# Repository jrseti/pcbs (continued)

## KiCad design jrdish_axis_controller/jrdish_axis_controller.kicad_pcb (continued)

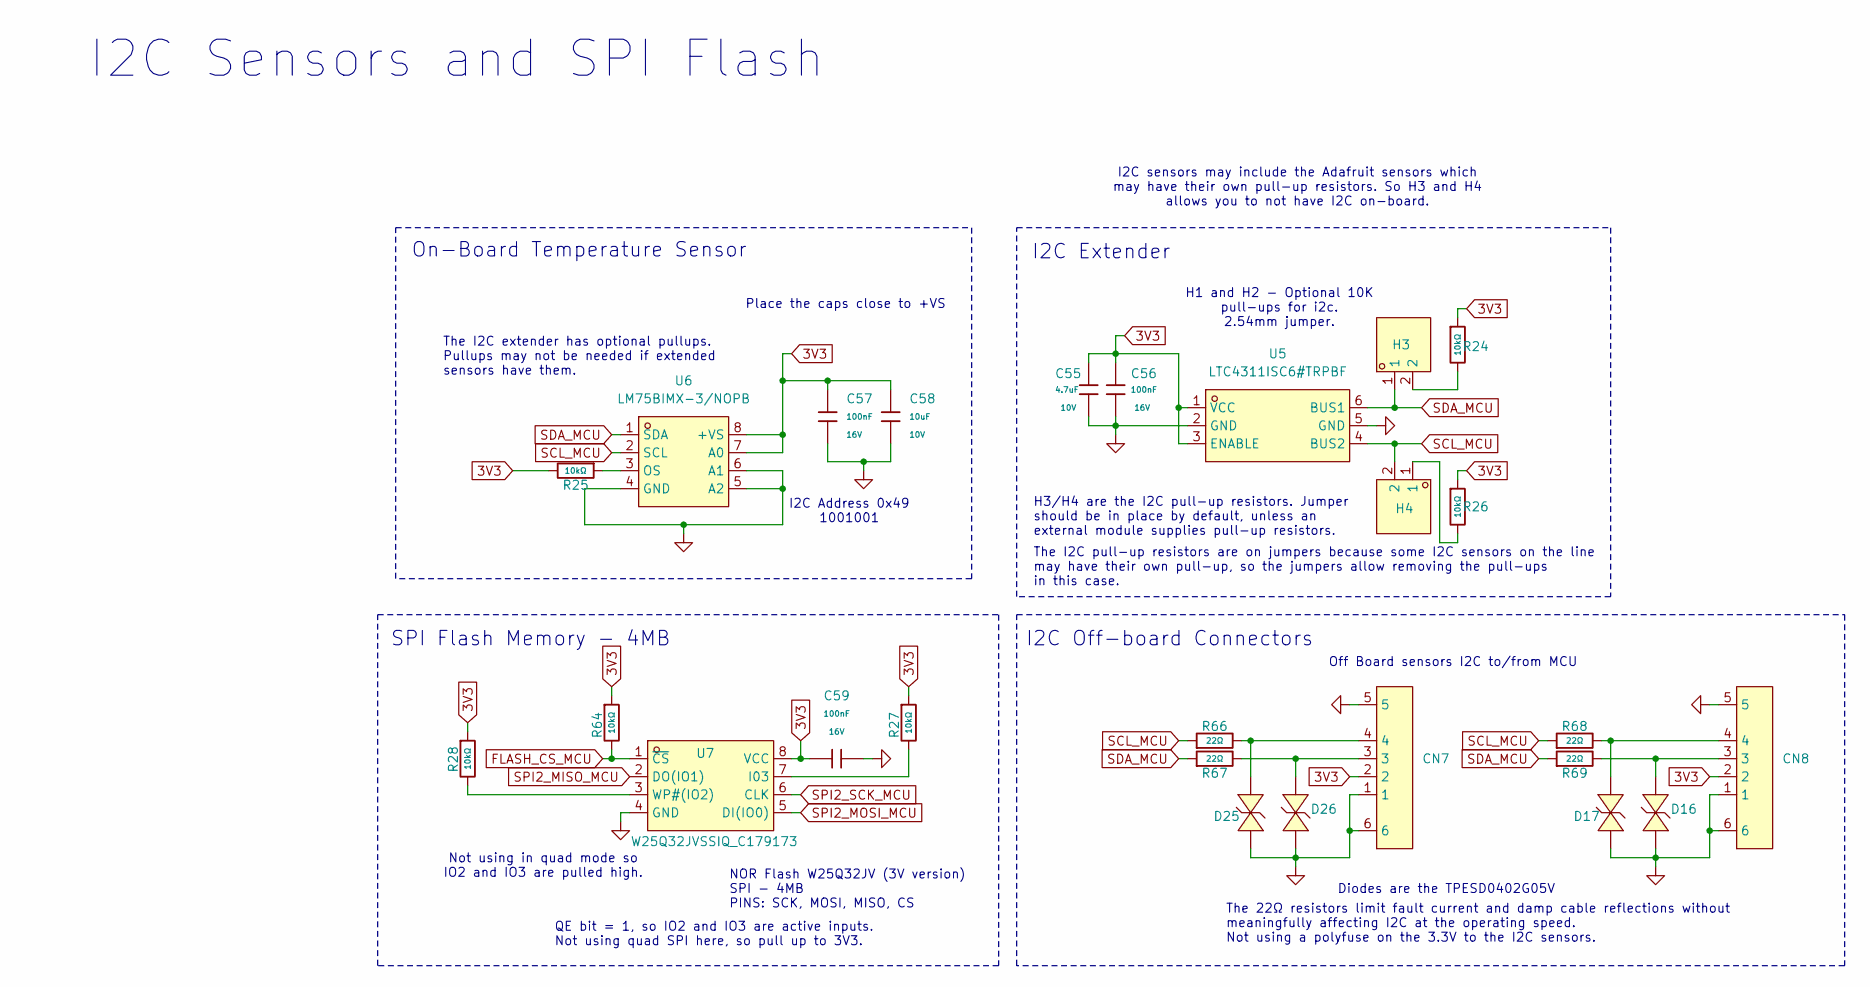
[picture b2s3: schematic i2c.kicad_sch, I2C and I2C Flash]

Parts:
C55: 4.7uF; C_0402; Voltage Rated 10V; Tolerance ±20%; Part CL05A475MP5NRNC; LCSC C23733
C56, C57, C59: 100nF; C_0402; Voltage Rated 16V; Tolerance ±10%; Part CL05B104KO5NNNC; LCSC C1525
C58: 10uF; C_0603; Voltage Rated 10V; Tolerance ±10%; Part CL10A106KP8NNNC; LCSC C19702
CN7, CN8: SM04B-SRSS-TB (LF)(SN); CONN-SMD_4P-P1.00_SM04B-SRSS-TB-LF-SN; LCSC Part C160404
D16, D17, D25, D26: TPESD0402G05V; D0402-BI; LCSC Part C558615
H3, H4: 210S-1*2P L=11.6MMGold-plated black; HDR-TH_2P-P2.54-V-M-1; MPN B-2100S02P-A110; LCSC Part C124375
R24, R25, R26, R27, R28, R64: 10kΩ; R_0402; Overload Voltage (Max) 50V; Tolerance ±1%; Part 0402WGF1002TCE; LCSC C173683
R66, R67, R68, R69: 22Ω; R_0402; Overload Voltage (Max) 50V; Tolerance ±1%; Part 0402WGF220JTCE; LCSC C25092
U5: LTC4311ISC6#TRPBF; SC-70-6_L2.2-W1.3-P0.65-LS2.2-BL; LCSC Part C688097
U6: LM75BIMX-3/NOPB; SOIC-8_L4.9-W3.9-P1.27-LS6.0-BL; MPN LM75BIMX-3/NOPB; LCSC Part C477980
U7: W25Q32JVSSIQ_C179173; SOIC-8_L5.3-W5.3-P1.27-LS8.0-BL; MPN W25Q32JVSSIQ; LCSC Part C179173

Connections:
FLASH_CS_MCU: R64.2, U7.1 (~CS); also elsewhere on the board
GND: C55.2, C56.2, C57.2, C58.2, C59.2, CN7.1, CN7.5, CN7.6, CN8.1, CN8.5, CN8.6, D16.2 (A), D17.2 (A), D25.2 (A), D26.2 (A), U5.2 (GND), U5.5 (GND), U6.4 (GND), U6.5 (A2), U6.6 (A1), U7.4 (GND); also elsewhere on the board
unnamed: CN8.3, D16.1 (K), R69.2
unnamed: CN8.4, D17.1 (K), R68.2
unnamed: CN7.4, D25.1 (K), R66.2
unnamed: CN7.3, D26.1 (K), R67.2
unnamed: H3.2, R24.2
unnamed: H4.1, R26.2
unnamed: R25.1, U6.3 (OS)
unnamed: R27.2, U7.7 (I03)
unnamed: R28.2, U7.3 (WP#(IO2))
SCL_MCU: H4.2, R66.1, R68.1, U5.4 (BUS2), U6.2 (SCL); also elsewhere on the board
SDA_MCU: H3.1, R67.1, R69.1, U5.6 (BUS1), U6.1 (SDA); also elsewhere on the board
SPI2_MISO_MCU: U7.2 (DO(IO1)); also elsewhere on the board
SPI2_MOSI_MCU: U7.5 (DI(IO0)); also elsewhere on the board
SPI2_SCK_MCU: U7.6 (CLK); also elsewhere on the board

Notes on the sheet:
H1 and H2 - Optional 10K pull-ups for i2c. 2.54mm jumper.
I2C Address 0x49 1001001
Off Board sensors I2C to/from MCU
NOR Flash W25Q32JV (3V version) SPI - 4MB PINS: SCK, MOSI, MISO, CS
I2C Off-board Connectors
I2C Extender
I2C Sensors and SPI Flash
H3/H4 are the I2C pull-up resistors. Jumper should be in place by default, unless an external module supplies pull-up resistors.
QE bit = 1, so IO2 and IO3 are active inputs. Not using quad SPI here, so pull up to 3V3.
I2C sensors may include the Adafruit sensors which may have their own pull-up resistors. So H3 and H4 allows you to not have I2C on-board.
The I2C pull-up resistors are on jumpers because some I2C sensors on the line may have their own pull-up, so the jumpers allow removing the pull-ups in this case.
Not using in quad mode so IO2 and IO3 are pulled high.
Place the caps close to +VS
On-Board Temperature Sensor
The I2C extender has optional pullups. Pullups may not be needed if extended sensors have them.
SPI Flash Memory - 4MB
The 22Ω resistors limit fault current and damp cable reflections without meaningfully affecting I2C at the operating speed. Not using a polyfuse on the 3.3V to the I2C sensors.
Diodes are the TPESD0402G05V

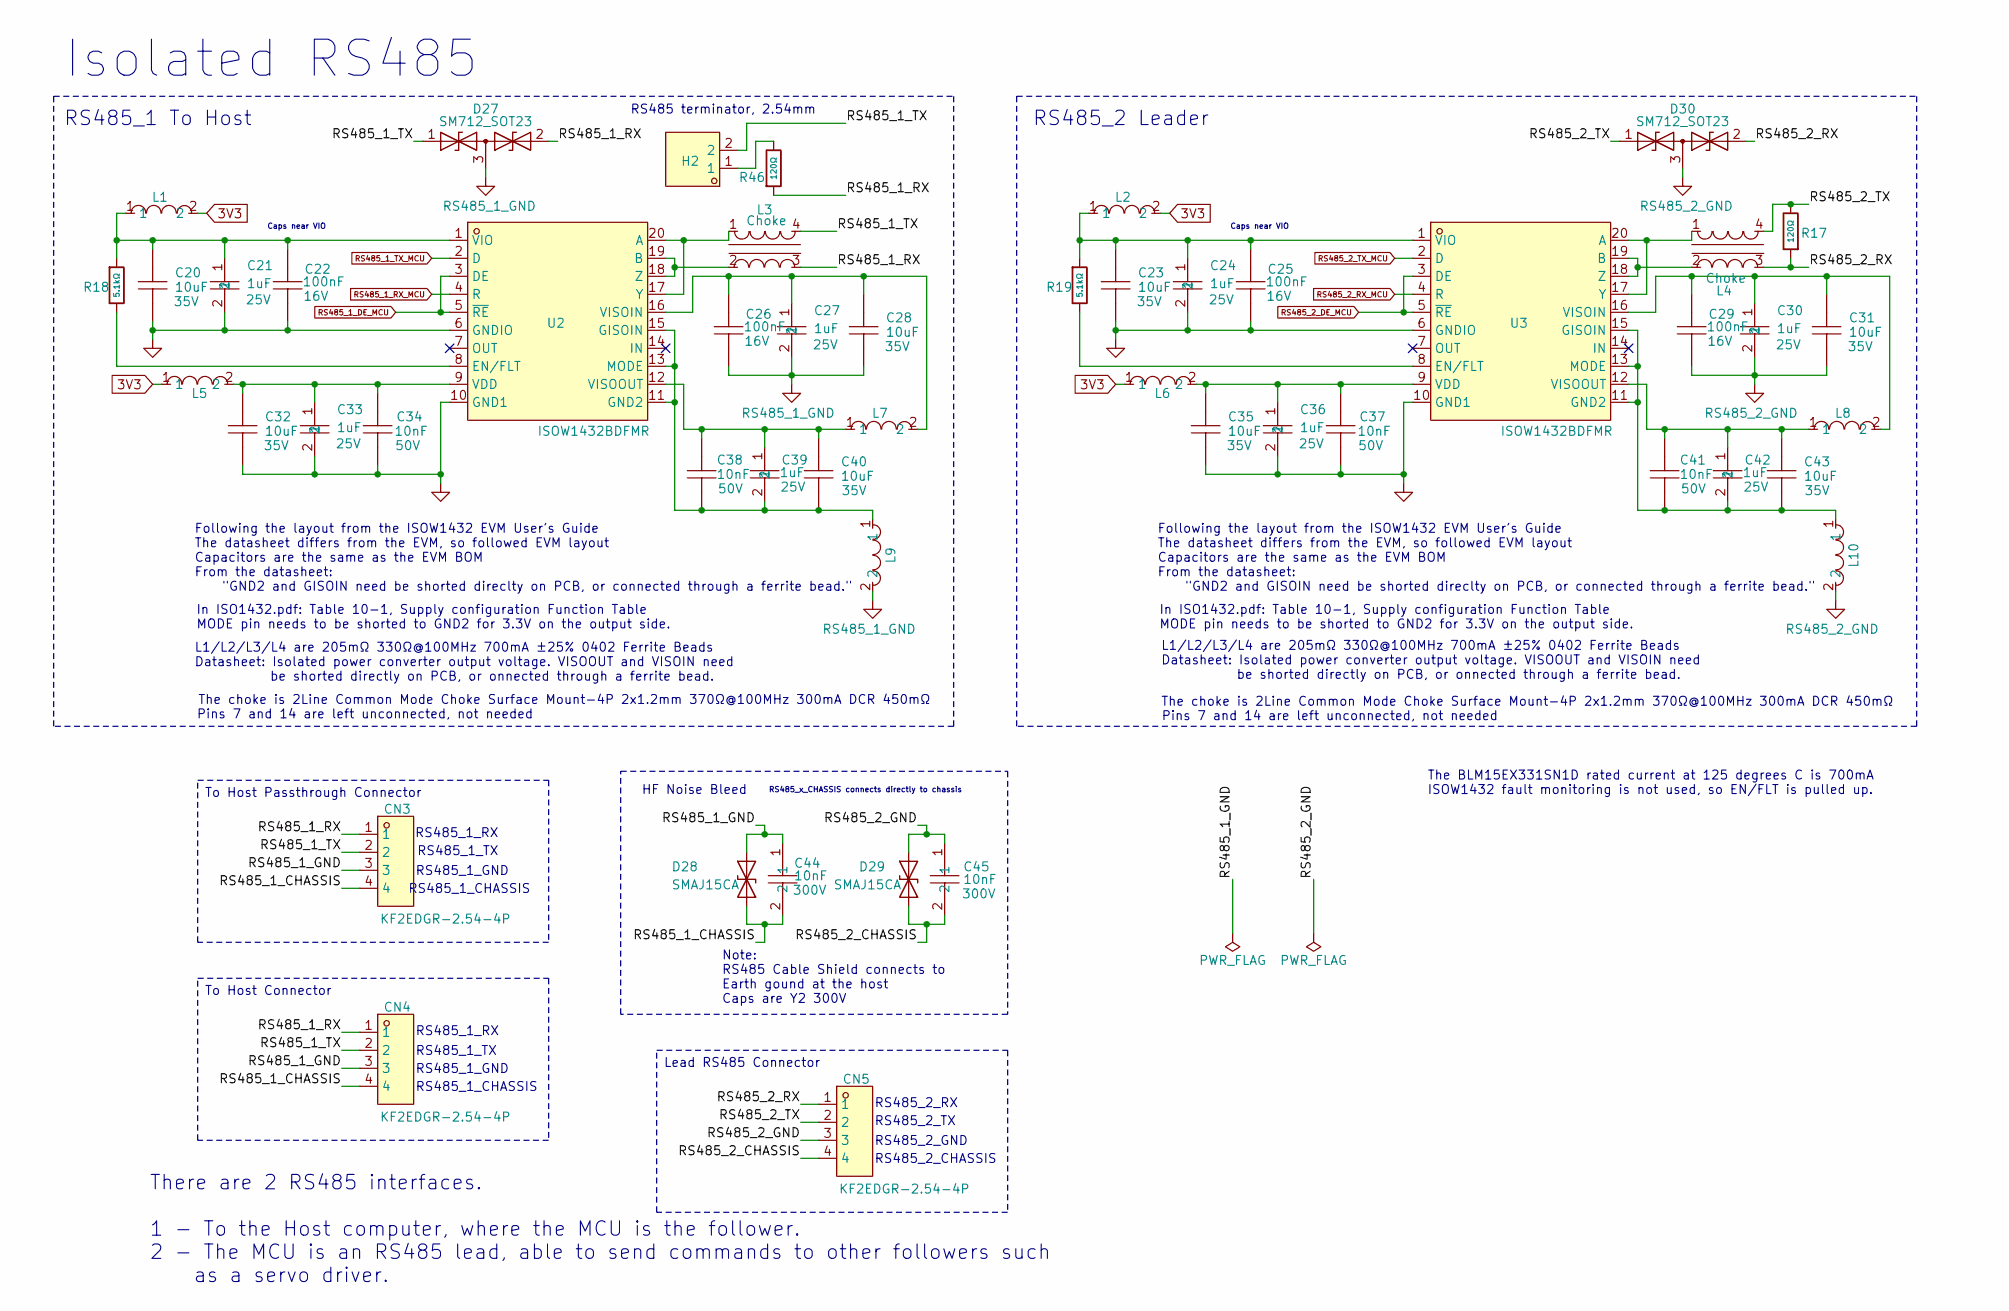
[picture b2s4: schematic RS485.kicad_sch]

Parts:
C20, C23, C28, C31, C32, C35, C40, C43: 10uF; C0805; Voltage Rating 35V; MPN GRM21BR6YA106KE43L; LCSC Part C162422
C21, C24, C27, C30, C33, C36, C39, C42: 1uF; C0603; Voltage Rated 25V; MPN CL10A105KA8NNNC; LCSC Part C5673
C22: 100nF; C0402; Voltage Rated 16V; Voltage 16V; MPN CL05B104KO5NNNC; LCSC Part C1525
C25, C26, C29: 100nF; C0402; Voltage Rated 16V; MPN CL05B104KO5NNNC; LCSC Part C1525
C34, C37, C38, C41: 10nF; C0402; Voltage Rating 50V; MPN 0402B103K500CT; LCSC Part C301927
C44, C45: 10nF; CAP-TH_L13.0-W6.0-P10.00-D1.2; Voltage rated 300V; MPN C43Q1103K40C80F; LCSC Part C328783
CN3, CN4, CN5: KF2EDGR-2.54-4P; CONN-TH_4P-P2.54_KF2EDGR-2.54-4P; LCSC Part C577596
D27, D30: SM712_SOT23; SOT-23; LCSC C172881
D28, D29: SMAJ15CA; D_SMA
H2: 210S-1*2P L=11.6MMGold-plated black; HDR-TH_2P-P2.54-V-M-1; MPN B-2100S02P-A110; LCSC Part C124375
L1, L2, L5, L6, L7, L8, L9, L10: BLM15EX331SN1D; L0402; MPN BLM15EX331SN1D; LCSC Part C596498
L3, L4: Choke; FILTER-SMD_4P-L2.0-W1.2-BL; MPN SMW2012B371BTE; LCSC Part C254903
R17, R46: 120Ω; R_0805; Overload Voltage (Max) 150V; Tolerance ±1%; Part 0805W8F1200T5E; LCSC C17437
R18, R19: 5.1kΩ; R_0402; Overload Voltage (Max) 50V; Tolerance ±1%; Part 0402WGF5101TCE; LCSC C25905
U2, U3: ISOW1432BDFMR; SOIC-20_L12.8-W7.5-P1.27-LS10.3-BL; MPN ISOW1432BDFMR; LCSC Part C5216543

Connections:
/RS485/RS485_1_CHASSIS: C44.2, CN3.4, CN4.4, D28.1 (A1)
/RS485/RS485_1_RX: CN3.1, CN4.1, D27.2 (A2), L3.3, R46.1
/RS485/RS485_1_TX: CN3.2, CN4.2, D27.1 (A1), H2.2, L3.4
/RS485/RS485_2_CHASSIS: C45.2, CN5.4, D29.1 (A1)
/RS485/RS485_2_RX: CN5.1, D30.2 (A2), L4.3, R17.1
/RS485/RS485_2_TX: CN5.2, D30.1 (A1), L4.4, R17.2
GND: C20.1, C21.2, C22.2, C23.1, C24.2, C25.2, C32.1, C33.2, C34.2, C35.1, C36.2, C37.2, U2.6 (GNDIO), U2.10 (GND1), U3.6 (GNDIO), U3.10 (GND1); also elsewhere on the board
unnamed: H2.1, R46.2
unnamed: L3.1, U2.17 (Y), U2.20 (A)
unnamed: L3.2, U2.18 (Z), U2.19 (B)
unnamed: R18.2, U2.8 (EN/FLT)
unnamed: C38.2, C39.2, C40.1, L9.1, U2.11 (GND2), U2.13 (MODE), U2.15 (GISOIN)
unnamed: C32.2, C33.1, C34.1, L5.2, U2.9 (VDD)
unnamed: C20.2, C21.1, C22.1, L1.1, R18.1, U2.1 (VIO)
unnamed: C26.1, C27.1, C28.2, L7.2, U2.16 (VISOIN)
unnamed: C38.1, C39.1, C40.2, L7.1, U2.12 (VISOOUT)
unnamed: L4.1, U3.17 (Y), U3.20 (A)
unnamed: L4.2, U3.18 (Z), U3.19 (B)
unnamed: R19.2, U3.8 (EN/FLT)
unnamed: C41.2, C42.2, C43.1, L10.1, U3.11 (GND2), U3.13 (MODE), U3.15 (GISOIN)
unnamed: C35.2, C36.1, C37.1, L6.2, U3.9 (VDD)
unnamed: C23.2, C24.1, C25.1, L2.1, R19.1, U3.1 (VIO)
unnamed: C29.1, C30.1, C31.2, L8.2, U3.16 (VISOIN)
unnamed: C41.1, C42.1, C43.2, L8.1, U3.12 (VISOOUT)
RS485_1_DE_MCU: U2.3 (DE), U2.5 (~RE); also elsewhere on the board
RS485_1_GND: C26.2, C27.2, C28.1, C44.1, CN3.3, CN4.3, D27.3 (common), D28.2 (A2), L9.2
RS485_1_RX_MCU: U2.4 (R); also elsewhere on the board
RS485_1_TX_MCU: U2.2 (D); also elsewhere on the board
RS485_2_DE_MCU: U3.3 (DE), U3.5 (~RE); also elsewhere on the board
RS485_2_GND: C29.2, C30.2, C31.1, C45.1, CN5.3, D29.2 (A2), D30.3 (common), L10.2
RS485_2_RX_MCU: U3.4 (R); also elsewhere on the board
RS485_2_TX_MCU: U3.2 (D); also elsewhere on the board

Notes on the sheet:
RS485_2_GND
RS485_2_TX
The BLM15EX331SN1D rated current at 125 degrees C is 700mA ISOW1432 fault monitoring is not used, so EN/FLT is pulled up.
RS485_1_GND
Following the layout from the ISOW1432 EVM User's Guide The datasheet differs from the EVM, so followed EVM layout Capacitors are the same as the EVM BOM From the datasheet: "GND2 and GISOIN need be shorted direclty on PCB, or connected through a ferrite bead."
In ISO1432.pdf: Table 10-1, Supply configuration Function Table MODE pin needs to be shorted to GND2 for 3.3V on the output side.
Note: RS485 Cable Shield connects to Earth gound at the host Caps are Y2 300V
Isolated RS485
RS485_1_RX
RS485_2_RX
Caps near VIO
RS485_2 Leader
RS485_2_CHASSIS
Pins 7 and 14 are left unconnected, not needed
RS485_1_CHASSIS
The choke is 2Line Common Mode Choke Surface Mount-4P 2x1.2mm 370Ω@100MHz 300mA DCR 450mΩ
L1/L2/L3/L4 are 205mΩ 330Ω@100MHz 700mA ±25% 0402 Ferrite Beads Datasheet: Isolated power converter output voltage. VISOOUT and VISOIN need be shorted directly on PCB, or onnected through a ferrite bead.
RS485 terminator, 2.54mm
RS485_1_TX
RS485_1 To Host
RS485_x_CHASSIS connects directly to chassis
There are 2 RS485 interfaces. 1 - To the Host computer, where the MCU is the follower. 2 - The MCU is an RS485 lead, able to send commands to other followers such as a servo driver.
HF Noise Bleed
Lead RS485 Connector
To Host Connector
To Host Passthrough Connector

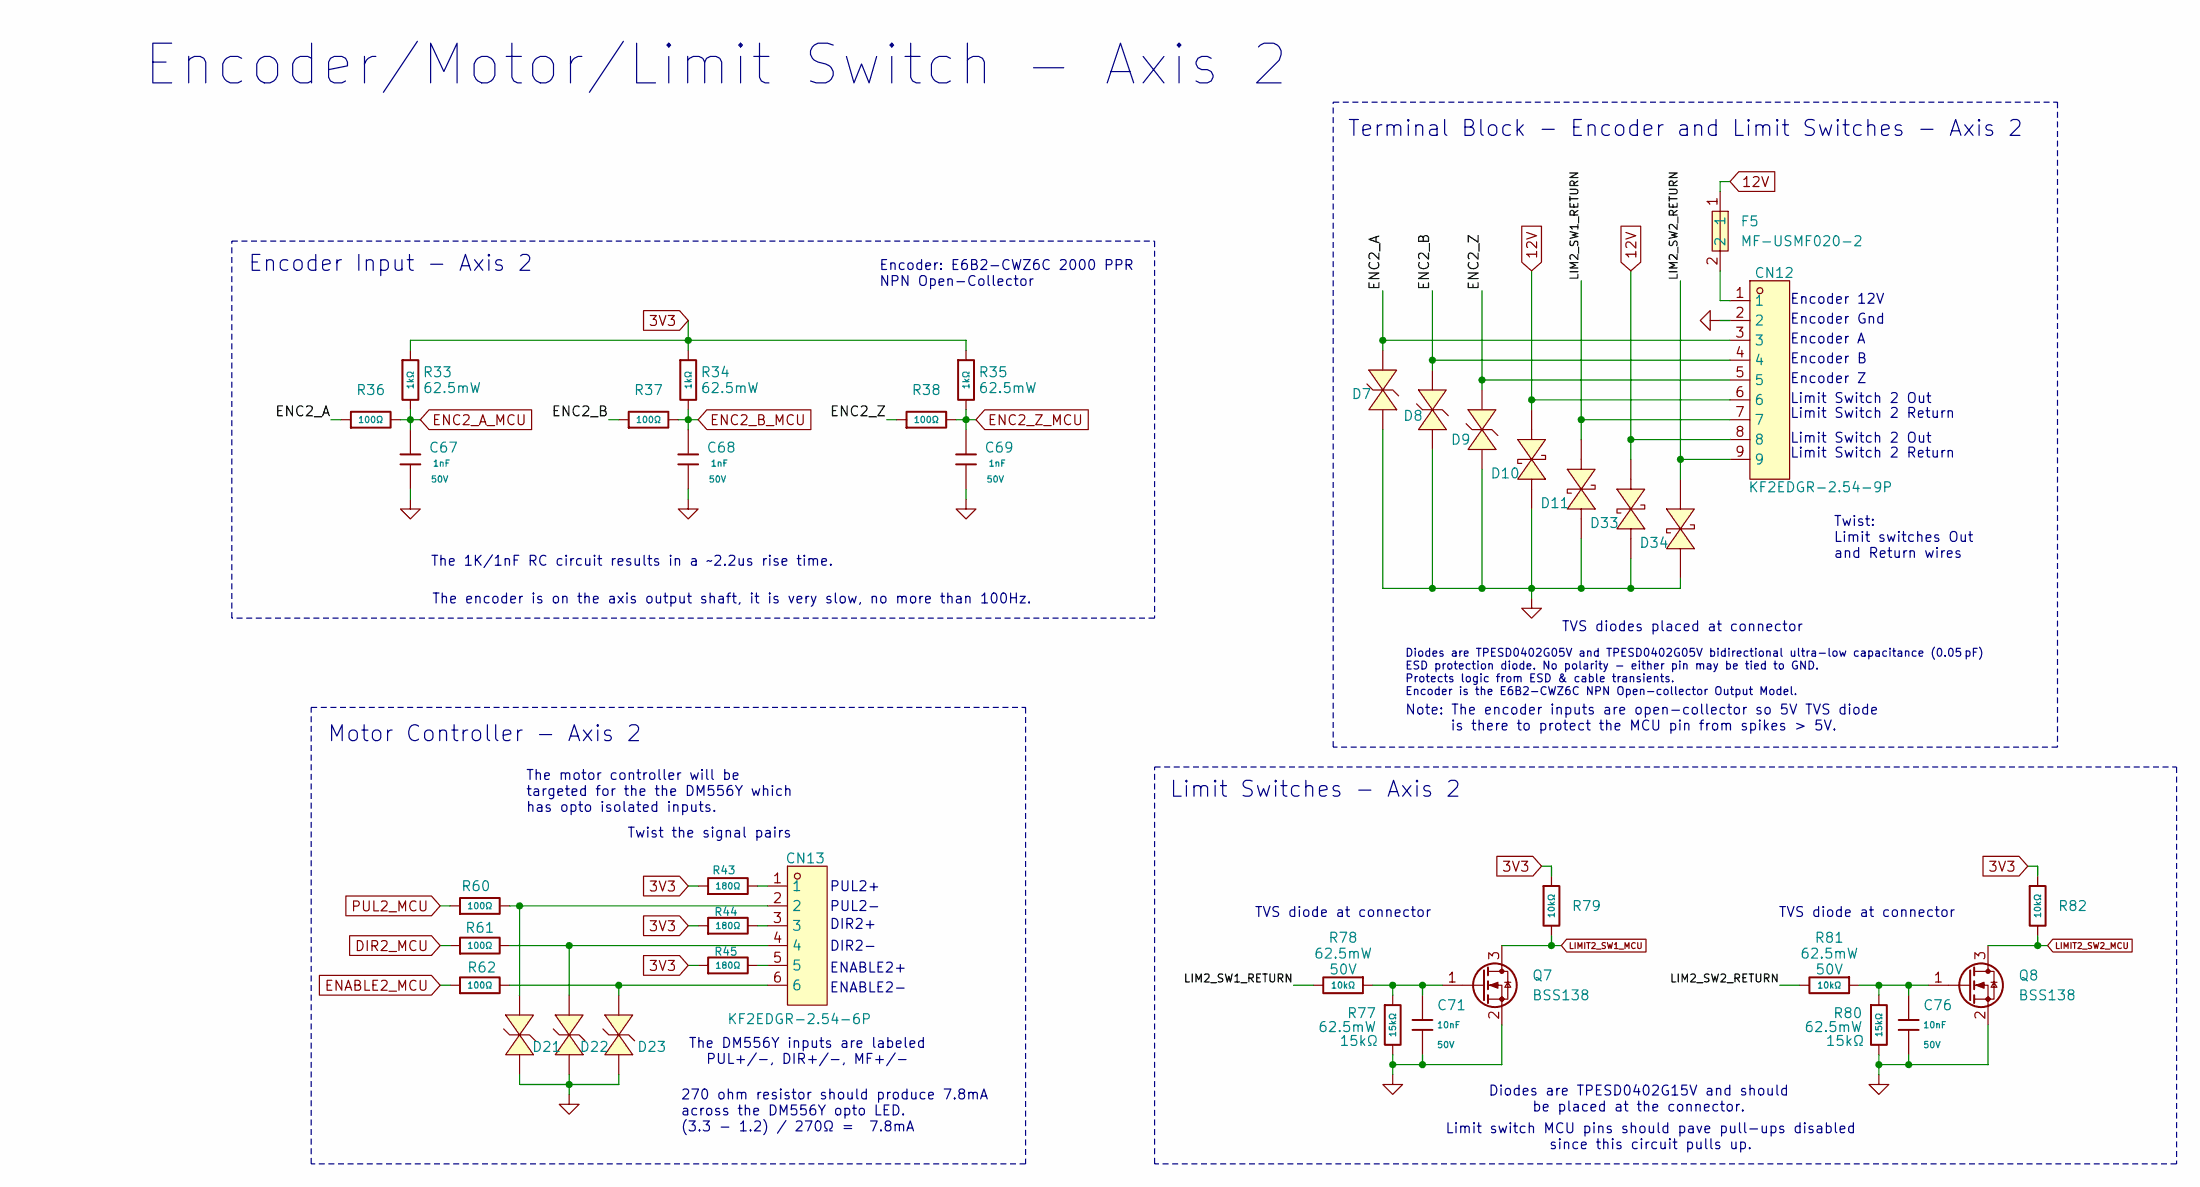
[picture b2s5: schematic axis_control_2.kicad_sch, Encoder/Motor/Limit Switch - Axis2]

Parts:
C67, C68, C69: 1nF; C_0402; Voltage Rated 50V; Tolerance ±10%; Part 0402B102K500NT; LCSC C1523
C71, C76: 10nF; C_0603; Voltage Rated 50V; Tolerance ±10%; Part 0603B103K500NT; LCSC C57112
CN12: KF2EDGR-2.54-9P; CONN-TH_9P-P2.54_KF2EDGR-2.54-9P; LCSC Part C577601
CN13: KF2EDGR-2.54-6P; CONN-TH_KF2EDGR-2.54-6P; LCSC Part C577598
D7, D8, D9, D21, D22, D23: TPESD0402G05V; D0402-BI; LCSC Part C558615
D10, D11, D33, D34: TPESD0402G15V; D0402-BI; MPN TPESD0402G15V; LCSC Part C558618
F5: MF-USMF020-2; F1210; MPN MF-USMF020-2; LCSC Part C210829
Q7, Q8: BSS138; SOT-23
R33, R34, R35: 1kΩ; R_0402; Overload Voltage (Max) 50V; Tolerance ±1%; Part 0402WGF1001TCE; LCSC C11702
R36, R37, R38, R60, R61, R62: 100Ω; R_0402; Overload Voltage (Max) 50V; Tolerance ±1%; Part 0402WGF1000TCE; LCSC C25076
R43, R44, R45: 180Ω; R_0603; Overload Voltage (Max) 75V; Tolerance ±1%; Part 0603WAF1800T5E; LCSC C22828
R77, R80: 15kΩ; R_0402; Overload Voltage (Max) 50V; Tolerance ±1%; Part 0402WGF1502TCE; LCSC C25756
R78, R79, R81, R82: 10kΩ; R_0402; Overload Voltage (Max) 50V; Tolerance ±1%; Part 0402WGF1002TCE; LCSC C173683

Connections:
12V: CN12.6, CN12.8, D10.2, D33.2, F5.1; also elsewhere on the board
/Axis Control - 2/ENC2_A: CN12.3, D7.1 (K), R36.1
/Axis Control - 2/ENC2_B: CN12.4, D8.1 (K), R37.1
/Axis Control - 2/ENC2_Z: CN12.5, D9.1 (K), R38.1
/Axis Control - 2/LIM2_SW1_RETURN: CN12.7, D11.2, R78.2
/Axis Control - 2/LIM2_SW2_RETURN: CN12.9, D34.2, R81.2
DIR2_MCU: R61.1; also elsewhere on the board
ENABLE2_MCU: R62.1; also elsewhere on the board
ENC2_A_MCU: C67.1, R33.2, R36.2; also elsewhere on the board
ENC2_B_MCU: C68.1, R34.2, R37.2; also elsewhere on the board
ENC2_Z_MCU: C69.1, R35.2, R38.2; also elsewhere on the board
GND: C67.2, C68.2, C69.2, C71.2, C76.2, CN12.2, D7.2 (A), D8.2 (A), D9.2 (A), D10.1, D11.1, D21.2 (A), D22.2 (A), D23.2 (A), D33.1, D34.1, Q7.2 (S), Q8.2 (S), R77.2, R80.2; also elsewhere on the board
LIMIT2_SW1_MCU: Q7.3 (D), R79.2; also elsewhere on the board
LIMIT2_SW2_MCU: Q8.3 (D), R82.2; also elsewhere on the board
unnamed: CN12.1, F5.2
unnamed: CN13.1, R43.2
unnamed: CN13.3, R44.2
unnamed: CN13.5, R45.2
unnamed: CN13.2, D21.1 (K), R60.2
unnamed: CN13.4, D22.1 (K), R61.2
unnamed: CN13.6, D23.1 (K), R62.2
unnamed: C71.1, Q7.1 (G), R77.1, R78.1
unnamed: C76.1, Q8.1 (G), R80.1, R81.1
PUL2_MCU: R60.1; also elsewhere on the board

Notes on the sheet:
Note: The encoder inputs are open-collector so 5V TVS diode is there to protect the MCU pin from spikes > 5V.
PUL2-
Diodes are TPESD0402G05V and TPESD0402G05V bidirectional ultra-low capacitance (0.05 pF) ESD protection diode. No polarity - either pin may be tied to GND. Protects logic from ESD & cable transients. Encoder is the E6B2-CWZ6C NPN Open-collector Output Model.
DIR2-
DIR2+
Limit Switch 2 Out
The 1K/1nF RC circuit results in a ~2.2us rise time.
Encoder: E6B2-CWZ6C 2000 PPR NPN Open-Collector
TVS diode at connector
Terminal Block - Encoder and Limit Switches - Axis 2
ENABLE2+
ENABLE2-
Encoder Input - Axis 2
Encoder A
The motor controller will be targeted for the the DM556Y which has opto isolated inputs.
Diodes are TPESD0402G15V and should be placed at the connector.
Encoder Z
Encoder 12V
PUL2+
Twist: Limit switches Out and Return wires
Motor Controller - Axis 2
Limit Switch 2 Return
The DM556Y inputs are labeled PUL+/-, DIR+/-, MF+/-
Encoder/Motor/Limit Switch - Axis 2
Limit switch MCU pins should pave pull-ups disabled since this circuit pulls up.
Encoder Gnd
The encoder is on the axis output shaft, it is very slow, no more than 100Hz.
Encoder B
TVS diodes placed at connector
Limit Switches - Axis 2
270 ohm resistor should produce 7.8mA across the DM556Y opto LED. (3.3 - 1.2) / 270Ω = 7.8mA
Twist the signal pairs

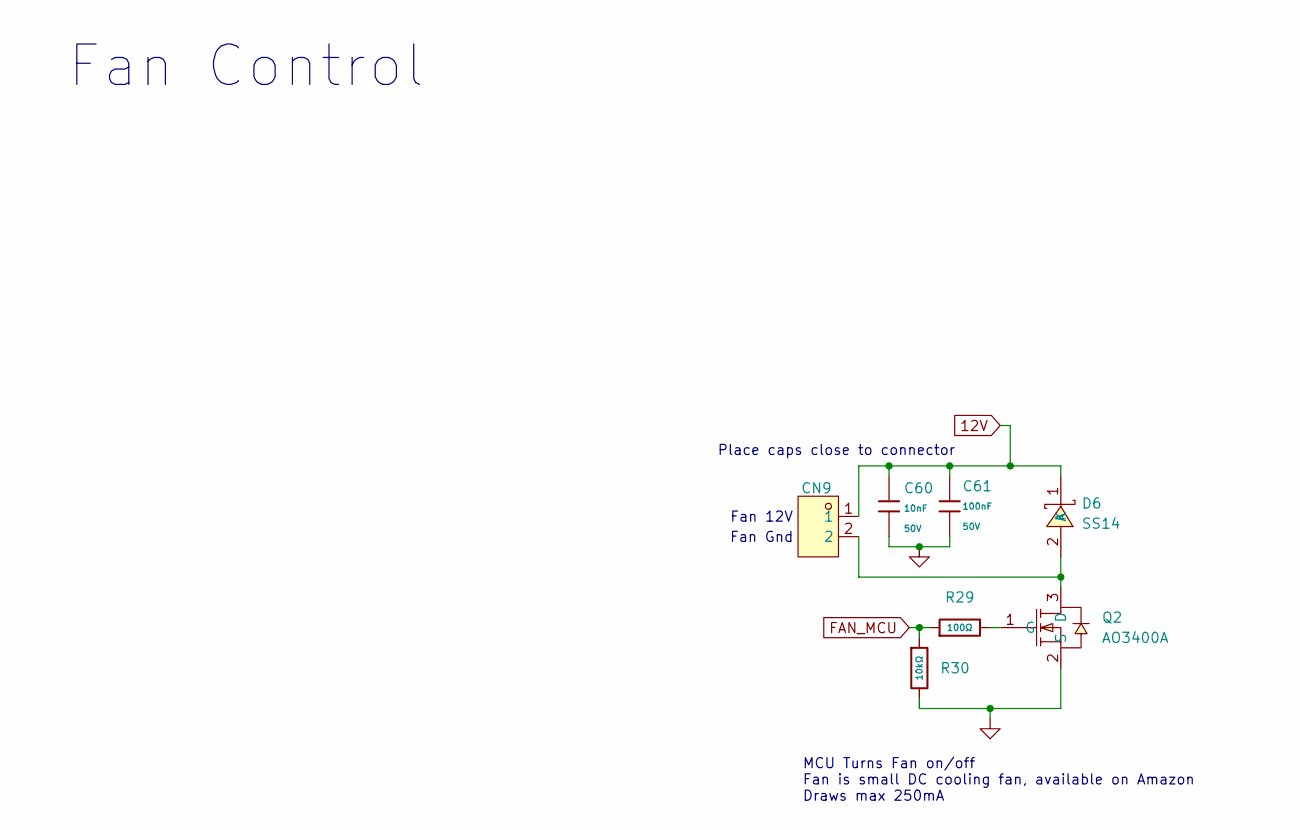
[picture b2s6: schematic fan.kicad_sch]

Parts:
C60: 10nF; C_0402; Voltage Rated 50V; Tolerance ±10%; Part CL05B103KB5NNNC; LCSC C15195
C61: 100nF; C_0402; Voltage Rated 50V; Tolerance ±10%; Part CL05B104KB54PNC; LCSC C307331
CN9: KF2EDGR-2.54-2P; CONN-TH_P2.54_KF2EDGR-2.54-2P; LCSC Part C577594
D6: SS14; SMA_L4.2-W2.6-LS5.0-RD_1; MPN SS14; LCSC Part C2480
Q2: AO3400A; SOT-23-3_L2.9-W1.3-P1.90-LS2.4-BR; MPN AO3400A; LCSC Part C20917
R29: 100Ω; R_0402; Overload Voltage (Max) 50V; Tolerance ±1%; Part 0402WGF1000TCE; LCSC C25076
R30: 10kΩ; R_0402; Overload Voltage (Max) 50V; Tolerance ±1%; Part 0402WGF1002TCE; LCSC C173683

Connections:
12V: C60.1, C61.1, CN9.1, D6.1 (K); also elsewhere on the board
FAN_MCU: R29.1, R30.1; also elsewhere on the board
GND: C60.2, C61.2, Q2.2 (S), R30.2; also elsewhere on the board
unnamed: CN9.2, D6.2 (A), Q2.3 (D)
unnamed: Q2.1 (G), R29.2

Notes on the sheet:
Fan Control
Fan 12V
Place caps close to connector
Fan Gnd
MCU Turns Fan on/off Fan is small DC cooling fan, available on Amazon Draws max 250mA

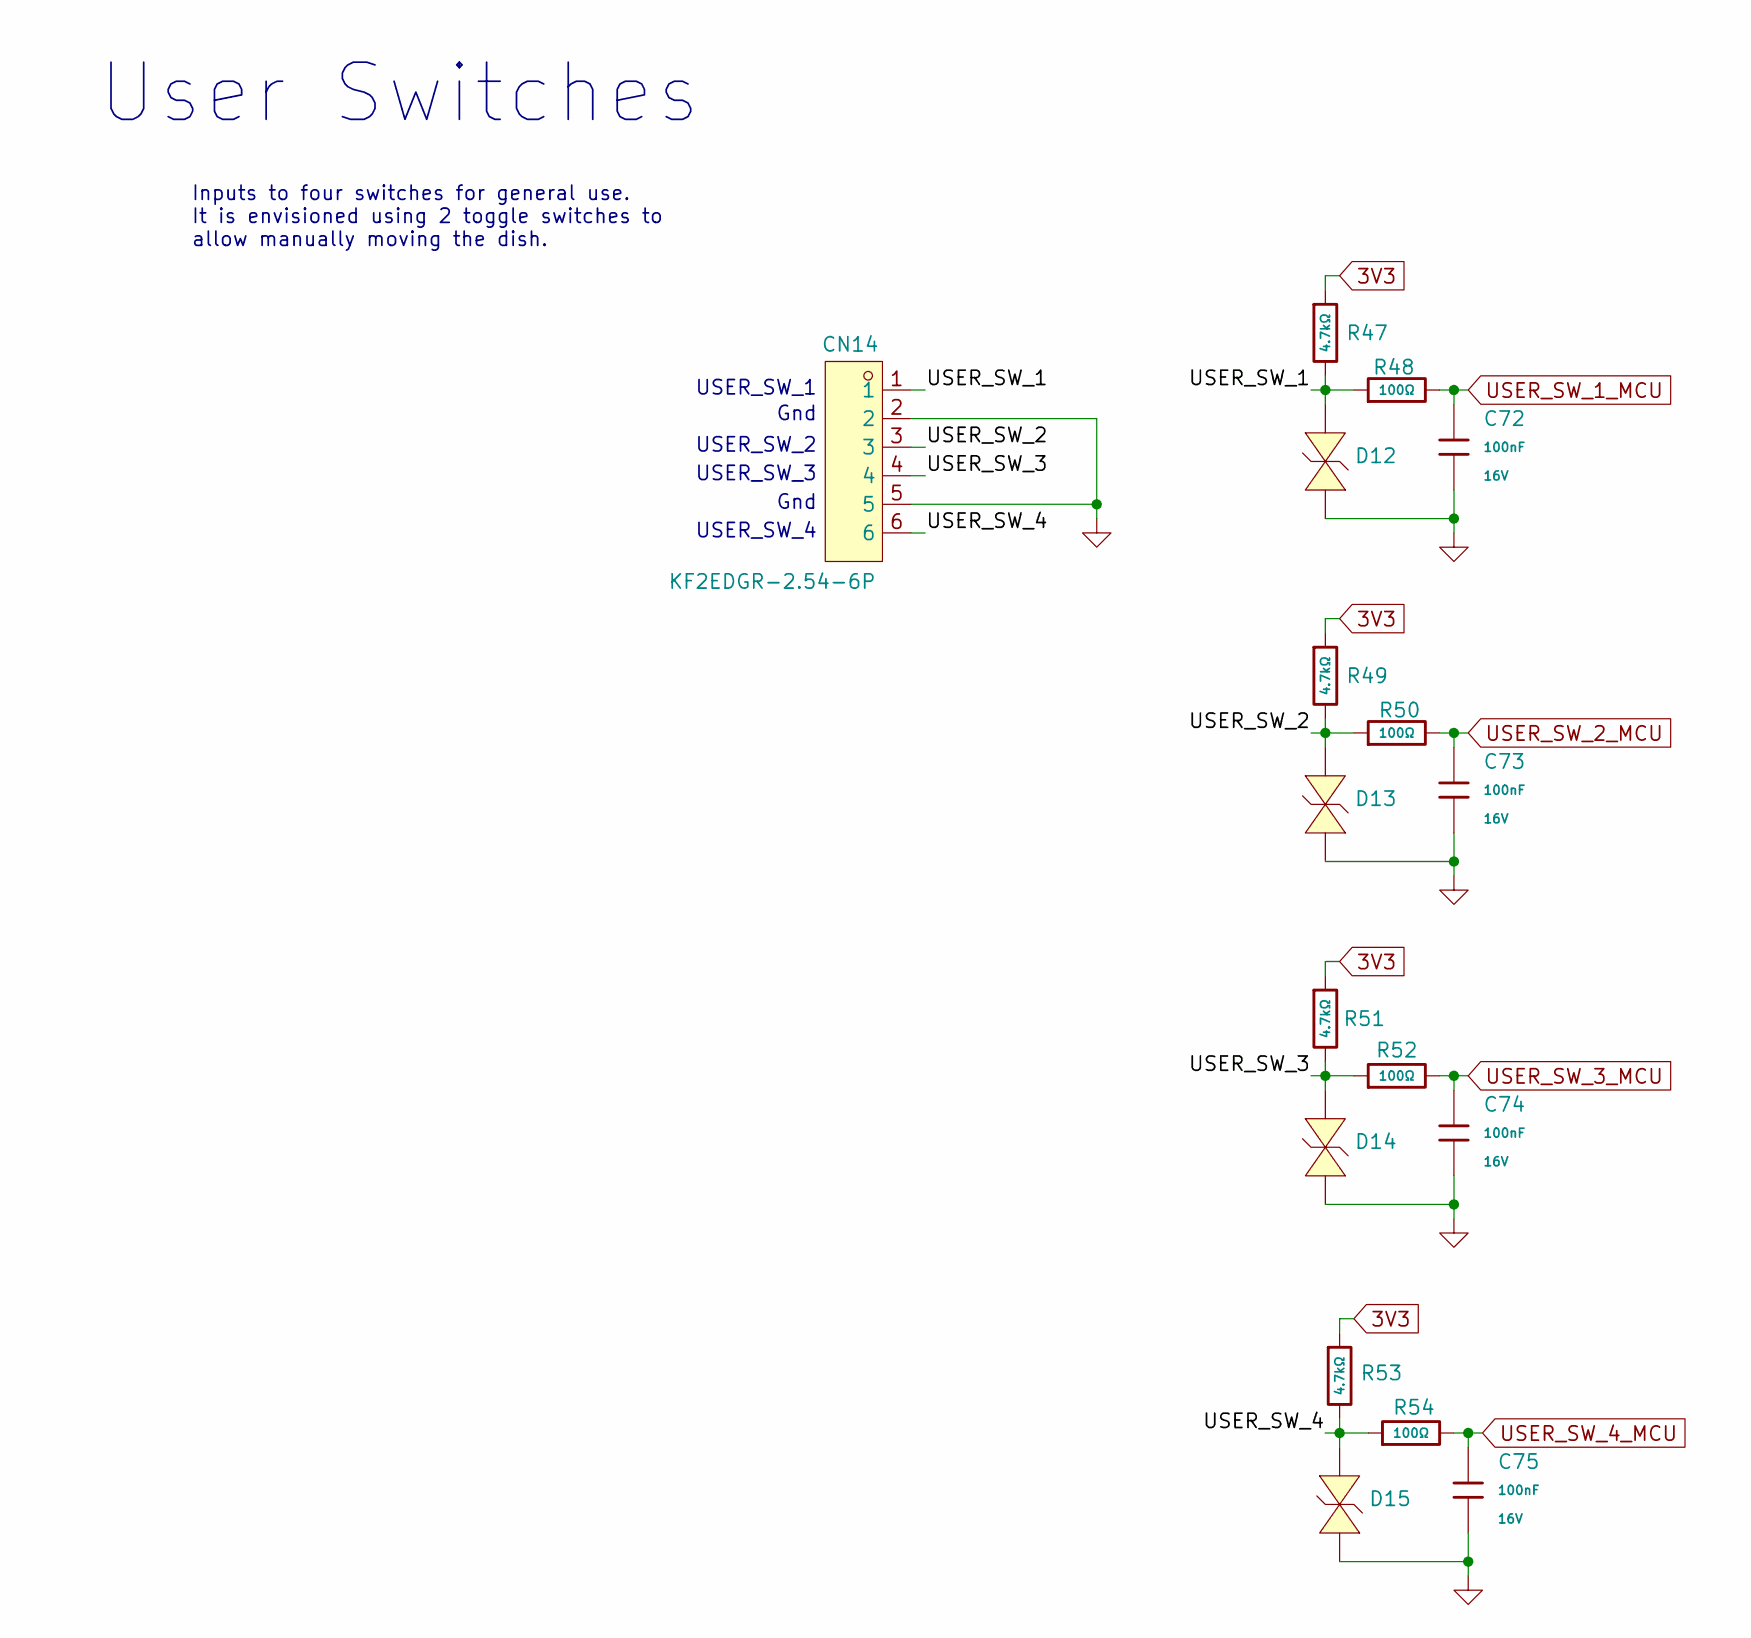
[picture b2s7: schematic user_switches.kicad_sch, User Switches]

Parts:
C72, C73, C74, C75: 100nF; C_0402; Voltage Rated 16V; Tolerance ±10%; Part CL05B104KO5NNNC; LCSC C1525
CN14: KF2EDGR-2.54-6P; CONN-TH_KF2EDGR-2.54-6P; LCSC Part C577598
D12, D13, D14, D15: TPESD0402G05V; D0402-BI; LCSC Part C558615
R47, R49, R51, R53: 4.7kΩ; R_0402; Overload Voltage (Max) 50V; Tolerance ±1%; Part 0402WGF4701TCE; LCSC C25900
R48, R50, R52, R54: 100Ω; R_0402; Overload Voltage (Max) 50V; Tolerance ±1%; Part 0402WGF1000TCE; LCSC C25076

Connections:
/User Switches/USER_SW_1: CN14.1, D12.1 (K), R47.2, R48.1
/User Switches/USER_SW_2: CN14.3, D13.1 (K), R49.2, R50.1
/User Switches/USER_SW_3: CN14.4, D14.1 (K), R51.2, R52.1
/User Switches/USER_SW_4: CN14.6, D15.1 (K), R53.2, R54.1
GND: C72.2, C73.2, C74.2, C75.2, CN14.2, CN14.5, D12.2 (A), D13.2 (A), D14.2 (A), D15.2 (A); also elsewhere on the board
USER_SW_1_MCU: C72.1, R48.2; also elsewhere on the board
USER_SW_2_MCU: C73.1, R50.2; also elsewhere on the board
USER_SW_3_MCU: C74.1, R52.2; also elsewhere on the board
USER_SW_4_MCU: C75.1, R54.2; also elsewhere on the board

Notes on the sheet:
USER_SW_2
USER_SW_3
USER_SW_1
Gnd
Inputs to four switches for general use. It is envisioned using 2 toggle switches to allow manually moving the dish.
User Switches
USER_SW_4

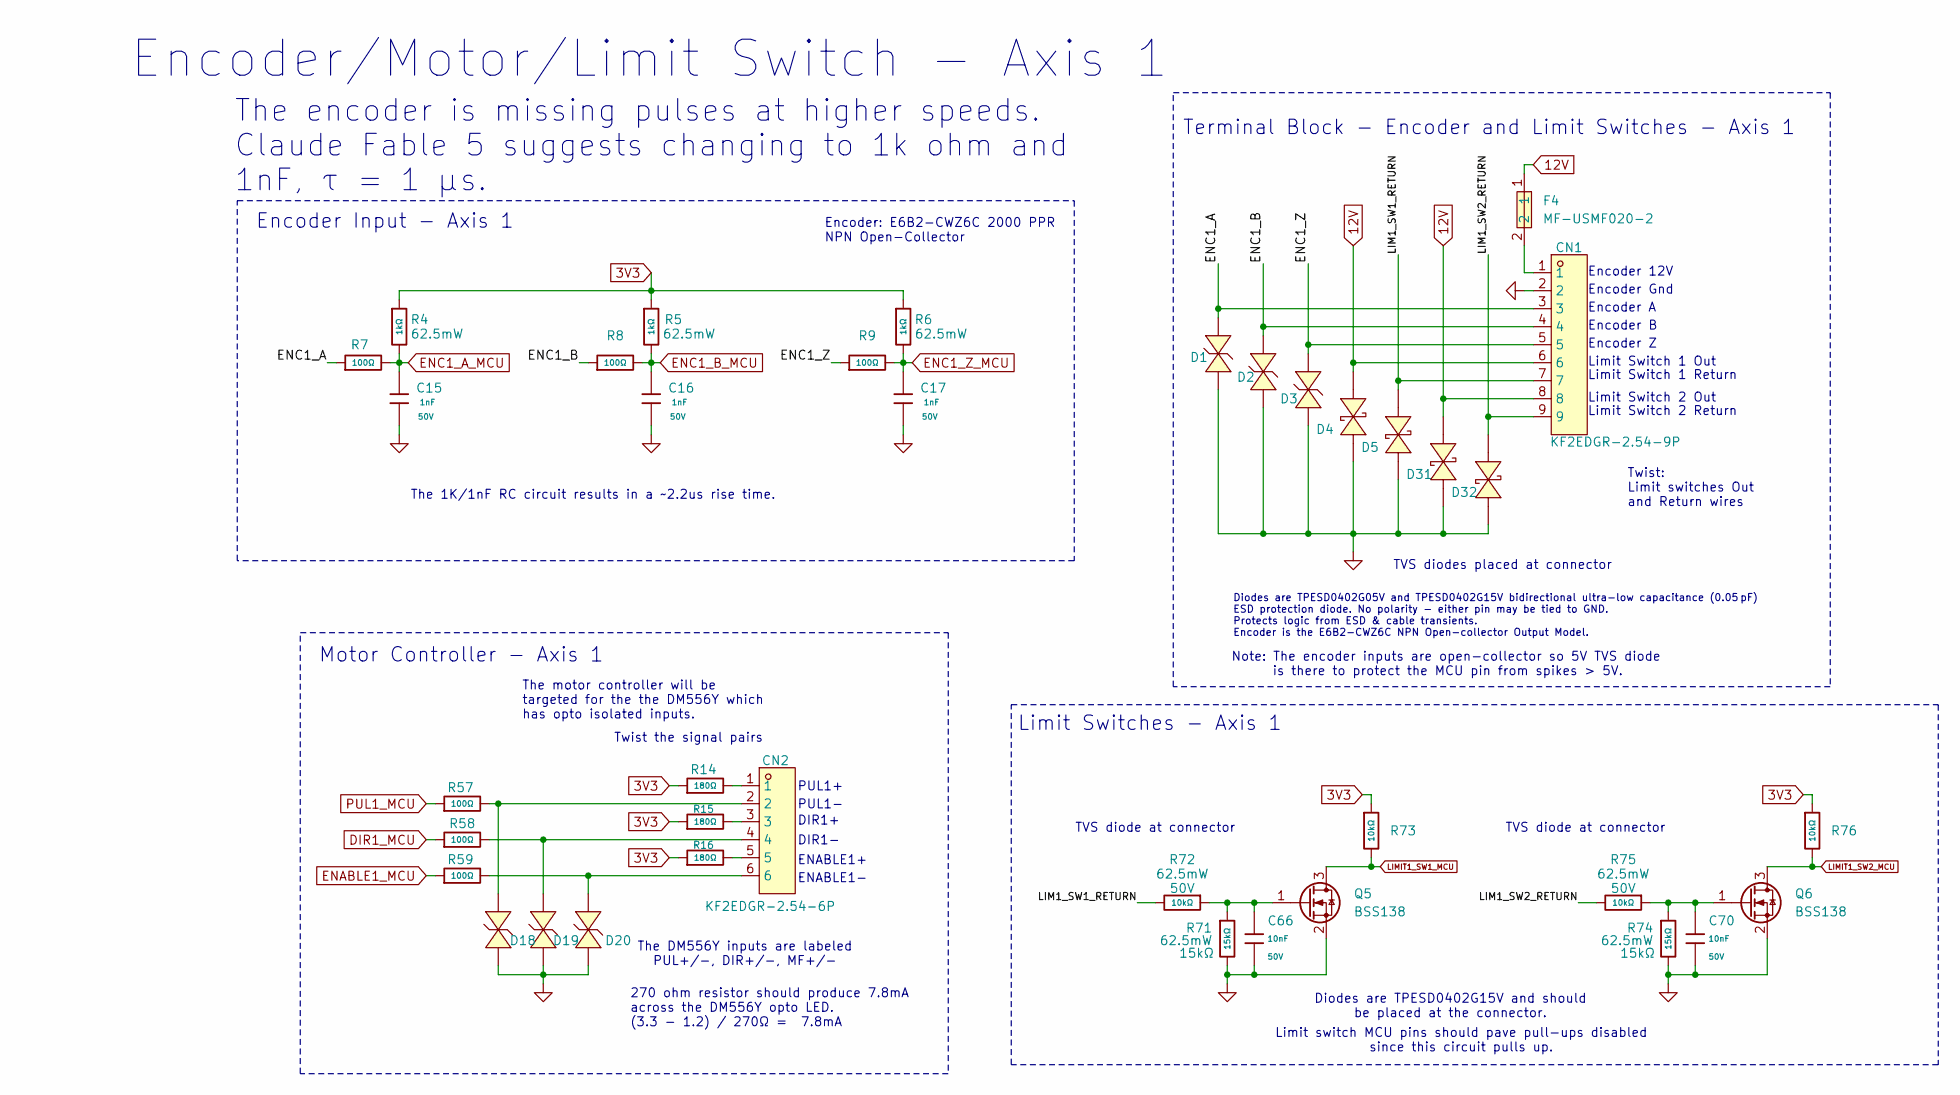
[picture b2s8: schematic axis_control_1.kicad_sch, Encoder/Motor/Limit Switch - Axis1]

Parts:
C15, C16, C17: 1nF; C_0402; Voltage Rated 50V; Tolerance ±10%; Part 0402B102K500NT; LCSC C1523
C66, C70: 10nF; C_0603; Voltage Rated 50V; Tolerance ±10%; Part 0603B103K500NT; LCSC C57112
CN1: KF2EDGR-2.54-9P; CONN-TH_9P-P2.54_KF2EDGR-2.54-9P; LCSC Part C577601
CN2: KF2EDGR-2.54-6P; CONN-TH_KF2EDGR-2.54-6P; LCSC Part C577598
D1, D2, D3, D18, D19, D20: TPESD0402G05V; D0402-BI; LCSC Part C558615
D4, D5, D31, D32: TPESD0402G15V; D0402-BI; MPN TPESD0402G15V; LCSC Part C558618
F4: MF-USMF020-2; F1210; MPN MF-USMF020-2; LCSC Part C210829
Q5, Q6: BSS138; SOT-23
R4, R5, R6: 1kΩ; R_0402; Overload Voltage (Max) 50V; Tolerance ±1%; Part 0402WGF1001TCE; LCSC C11702
R7, R8, R9, R57, R58, R59: 100Ω; R_0402; Overload Voltage (Max) 50V; Tolerance ±1%; Part 0402WGF1000TCE; LCSC C25076
R14, R15, R16: 180Ω; R_0603; Overload Voltage (Max) 75V; Tolerance ±1%; Part 0603WAF1800T5E; LCSC C22828
R71, R74: 15kΩ; R_0402; Overload Voltage (Max) 50V; Tolerance ±1%; Part 0402WGF1502TCE; LCSC C25756
R72, R73, R75, R76: 10kΩ; R_0402; Overload Voltage (Max) 50V; Tolerance ±1%; Part 0402WGF1002TCE; LCSC C173683

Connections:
12V: CN1.6, CN1.8, D4.2, D31.2, F4.1; also elsewhere on the board
/Axis Control - 1/ENC1_A: CN1.3, D1.1 (K), R7.1
/Axis Control - 1/ENC1_B: CN1.4, D2.1 (K), R8.1
/Axis Control - 1/ENC1_Z: CN1.5, D3.1 (K), R9.1
/Axis Control - 1/LIM1_SW1_RETURN: CN1.7, D5.2, R72.2
/Axis Control - 1/LIM1_SW2_RETURN: CN1.9, D32.2, R75.2
DIR1_MCU: R58.1; also elsewhere on the board
ENABLE1_MCU: R59.1; also elsewhere on the board
ENC1_A_MCU: C15.1, R4.2, R7.2; also elsewhere on the board
ENC1_B_MCU: C16.1, R5.2, R8.2; also elsewhere on the board
ENC1_Z_MCU: C17.1, R6.2, R9.2; also elsewhere on the board
GND: C15.2, C16.2, C17.2, C66.2, C70.2, CN1.2, D1.2 (A), D2.2 (A), D3.2 (A), D4.1, D5.1, D18.2 (A), D19.2 (A), D20.2 (A), D31.1, D32.1, Q5.2 (S), Q6.2 (S), R71.2, R74.2; also elsewhere on the board
LIMIT1_SW1_MCU: Q5.3 (D), R73.2; also elsewhere on the board
LIMIT1_SW2_MCU: Q6.3 (D), R76.2; also elsewhere on the board
unnamed: CN1.1, F4.2
unnamed: CN2.1, R14.2
unnamed: CN2.3, R15.2
unnamed: CN2.5, R16.2
unnamed: CN2.2, D18.1 (K), R57.2
unnamed: CN2.4, D19.1 (K), R58.2
unnamed: CN2.6, D20.1 (K), R59.2
unnamed: C66.1, Q5.1 (G), R71.1, R72.1
unnamed: C70.1, Q6.1 (G), R74.1, R75.1
PUL1_MCU: R57.1; also elsewhere on the board

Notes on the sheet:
Limit Switches - Axis 1
Note: The encoder inputs are open-collector so 5V TVS diode is there to protect the MCU pin from spikes > 5V.
TVS diode at connector
Motor Controller - Axis 1
Encoder Input - Axis 1
Diodes are TPESD0402G05V and TPESD0402G15V bidirectional ultra-low capacitance (0.05 pF) ESD protection diode. No polarity - either pin may be tied to GND. Protects logic from ESD & cable transients. Encoder is the E6B2-CWZ6C NPN Open-collector Output Model.
Twist: Limit switches Out and Return wires
ENABLE1+
Encoder/Motor/Limit Switch - Axis 1
270 ohm resistor should produce 7.8mA across the DM556Y opto LED. (3.3 - 1.2) / 270Ω = 7.8mA
Encoder: E6B2-CWZ6C 2000 PPR NPN Open-Collector
The encoder is missing pulses at higher speeds. Claude Fable 5 suggests changing to 1k ohm and 1nF, τ = 1 µs.
Twist the signal pairs
PUL1-
Limit Switch 1 Return
Encoder B
DIR1+
Limit switch MCU pins should pave pull-ups disabled since this circuit pulls up.
DIR1-
Limit Switch 2 Return
Encoder A
Encoder Gnd
The DM556Y inputs are labeled PUL+/-, DIR+/-, MF+/-
The 1K/1nF RC circuit results in a ~2.2us rise time.
Terminal Block - Encoder and Limit Switches - Axis 1
PUL1+
The motor controller will be targeted for the the DM556Y which has opto isolated inputs.
ENABLE1-
Limit Switch 2 Out
Encoder 12V
Encoder Z
Limit Switch 1 Out
TVS diodes placed at connector
Diodes are TPESD0402G15V and should be placed at the connector.

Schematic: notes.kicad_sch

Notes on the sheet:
Purpose: Control dual axes of a motor controlled system. - Modbus commands over isolated RS485 from a host. - MCU outputs motor PWM, direction, enable/disable - Input from encoder connected to motor output - Host provides configuration and position commands - MCU runs a PID loop to position/move mo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
MCU is the STM32G474CET6, 64-pin LQFP64 package Speed and position connands are received from a host over RS485. Encoder is the E6B2-CWZ6C. Motor Controller: DM556Y. 2-Wire program/debug connector with SWO. I2C for reading I2C sensors. 2 Limit switches. USART communication to Host. 16MHz oscillator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
Changes for V1.1 - Encoder RC values need changing for tighter timing - DONE - On/Off switch label reversed - DONE - Direct plugin for MAX-M10S GPS - DONE - Programming cable changed to 14 pins for STLINK-V3MINIE -DONE - Clearer Text on board - Done
NOTES
This STM32 can be clocked up to 170MHz. It was decided to decrease this to 48MHz due to RFI concerns. The 48MHz produces much weaker harmonics above 1GHz compared to 170MHz. If speed ever becomes a concern the clock rate can be increased.
